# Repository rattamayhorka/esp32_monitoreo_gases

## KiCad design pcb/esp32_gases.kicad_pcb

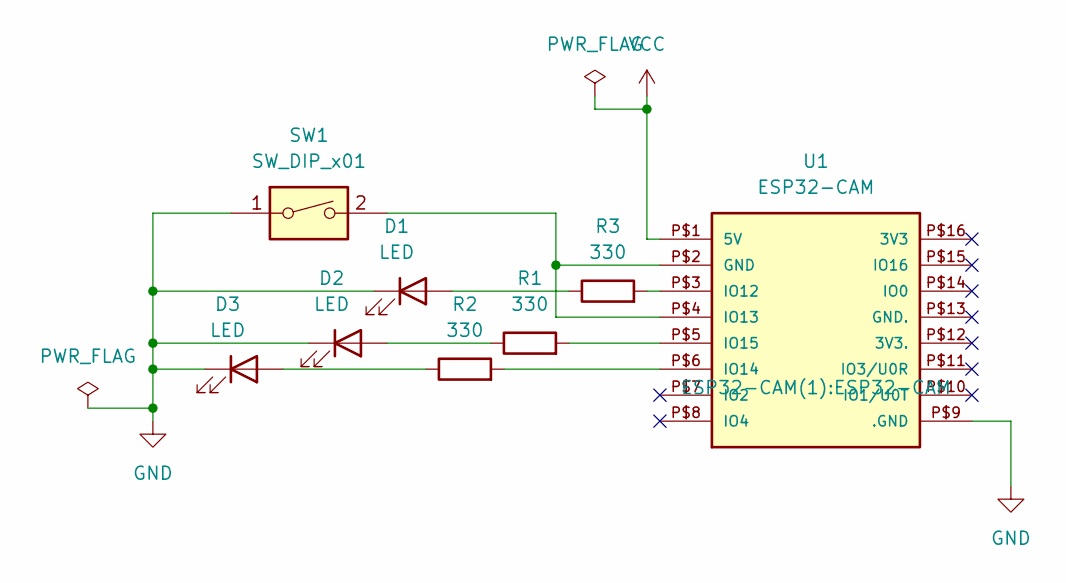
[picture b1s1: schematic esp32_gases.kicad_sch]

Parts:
D1, D2, D3: LED; LED_D5.0mm
R1, R2, R3: 330; R_Box_L13.0mm_W4.0mm_P9.00mm
SW1: SW_DIP_x01; SW_PUSH_6mm
U1: ESP32-CAM

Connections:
GND: D1.1 (K), D2.1 (K), D3.1 (K), SW1.1, U1.P$9 (.GND)
unnamed: D1.2 (A), R3.1
unnamed: D2.2 (A), R1.1
unnamed: D3.2 (A), R2.1
unnamed: SW1.2, U1.P$2 (GND), U1.P$4 (IO13)
unnamed: R3.2, U1.P$3 (IO12)
unnamed: R2.2, U1.P$6 (IO14)
unnamed: R1.2, U1.P$5 (IO15)
VCC: U1.P$1 (5V)

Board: 2 copper layers, 8 parts (0 on the bottom side), 8 nets, no tracks yet.

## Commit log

2024-08-20 primero
2024-08-20 agrego scripts de google
2024-08-20 cambio nombre carpeta
2025-04-07 actualizacion
2025-04-07 actualizacion con codigo arduino
2025-04-07 actualizacion con pcb
